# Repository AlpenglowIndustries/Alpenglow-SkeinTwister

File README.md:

# Alpenglow-SkeinTwister
The main open-source hardware repo for the Alpenglow Yarn SkeinTwister.  Start here, repo for the SkeinTwister software is [here](https://github.com/AlpenglowIndustries/SkeinTwisterCode).

Hello my friends.  As one of the final acts of Alpenglow Industries, we are open-sourcing the SkeinTwister design under a permissive CERN open hardware v2 license.  The text of the license is included in this repo, what it practically means is that as long as you attribute our original work, you can reproduce anything in this repo and even sell it.  

The [Alpenglow YouTube channel](https://www.youtube.com/watch?v=4FvFv4GcJJE&list=PLGswnsgctcE1kCAfXg5c3xEA6l_XDLfXw&pp=sAgC) has videos on assembly/disassembly and repair.

Note that we were purchasing parts and materials in large batches, so our sources that are listed in the SkeinTwister BOM spreadsheet may or may not be relevant for you. Use it as a starting point. The ReadMe docs in each folder will have more info about the parts that folder describes.

If you would like to reproduce this design and need help, Carrie Sundra is available to hire for consulting and for manufacturing the custom circuit boards.  You can reach out to her via [Discord](https://discord.com/users/461976578734161920) or [this email](mailto:info@alpenglowyarn.com) for now.  She is willing to do one free 30 minute video chat with anyone who is interested in reproducing the design, after that she may have time available at her hourly consulting rate.

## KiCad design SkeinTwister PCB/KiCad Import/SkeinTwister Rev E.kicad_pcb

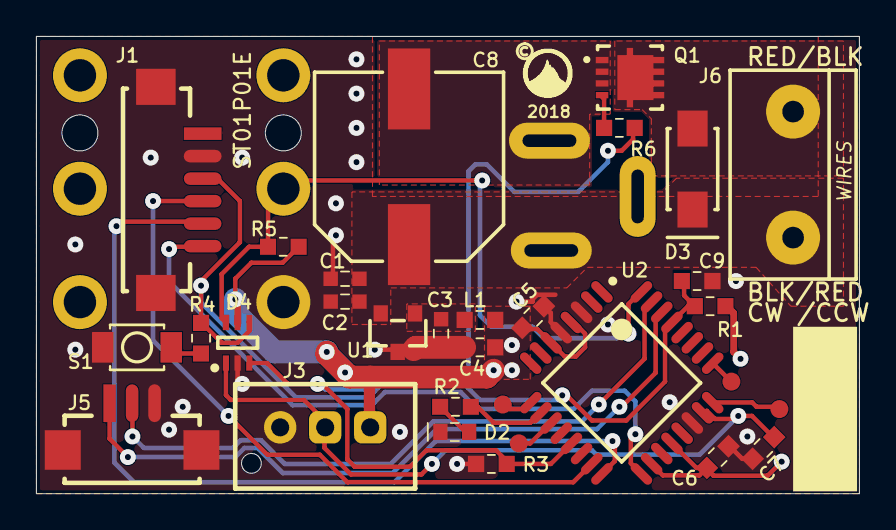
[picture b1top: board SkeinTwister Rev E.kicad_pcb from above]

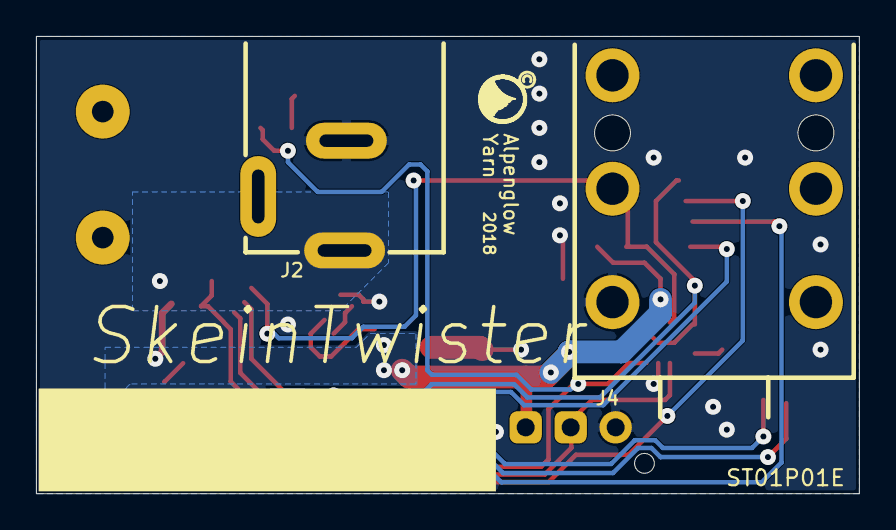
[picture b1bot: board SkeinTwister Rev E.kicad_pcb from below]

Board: 2 copper layers, 45.7 x 25.4 mm, 33 parts (2 on the bottom side), 22 nets.

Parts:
C1: 1.0; 0603
C2, C3, C5, C6, C7, C9: 0.1; 0603
C4: 10; 0603
C8: 820; CAP-10MM
D2: LED; 0603+
D3: DIODE, SM SIG; SMA
D4: TVS; SOT-363
J1: ISP Program; DF13C-6P-1.25V
J2: POWER; CONN-JACK-2MM - slots - M3
J3: KNOB; JST-XH-3
J4: FOOT PEDAL; AUDIO-6.35MM-RTA
J5: SERIAL; DF13C-3P-1.25V
J6: ?; OSTTE021104
L1: FERRITE, 0603; 0603
Q1: N; DFN8_3X3MM
R1, R3, R5: 10.0k; 0603
R2: 1.00k; 0603
R4: DNP (100); 0603
R6: 100; 0603
S1: DNP; PB-3.0X2.5-SMT
TP1, TP2, TP3, TP4: TESTPOINT; TP-1.0MM
U1: TLV76050; SOT-23
U2: ATMEGA328P_v2; TQFP-32

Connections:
5V: C4.1, C5.1, C6.1, D4.5, J3.3, L1.2, R1.2, R5.2, U2.4, U2.6, U2.18, U2.20
5V_UF: C3.1, L1.1, U1.1
12V: C1.1, C2.1, C8.1, D3.K, J2.1, J6.1, U1.2
FOOTPEDAL: D4.6, J4.4, R5.1, U2.32
GND: C1.2, C2.2, C3.2, C4.2, C5.2, C6.2, C7.2, C8.2, C9.2, D2.2, D4.2, J1.2, J1.7, J1.8, J2.2, J3.1, J4.6, J5.3, J5.4, J5.5, Q1.S, R3.1, S1.1, U1.3, U2.3, U2.5, U2.22
KNOB: C7.1, D4.1, J3.2, U2.23
LED: R2.2, U2.10
MISO: J1.5, U2.16
MOSI: J1.4, U2.15
NetD2_1: D2.1, R2.1
NetD3_A: D3.A, J6.2, Q1.D
NetQ1_G: Q1.G, R6.1
NetR4_2: R4.2, S1.2
NetTP1_1: TP1.1, U2.25
NetTP2_1: TP2.1, U2.24
NetTP3_1: TP3.1, U2.9
NetTP4_1: TP4.1, U2.11
ON/OFF: D4.3, R3.2, R6.2, U2.13
RESET: C9.1, D4.4, J1.3, R1.1, R4.1, U2.29
RXD: J5.1, U2.30
SCK: J1.6, U2.17
TXD: J5.2, U2.31

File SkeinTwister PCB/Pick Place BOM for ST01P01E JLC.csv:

Designator,Comment,Layer,Footprint,Mid X,Mid Y,Rotation
C1,1,Top,0603,17.145,11.938,180
C2,0.1,Top,0603,17.145,10.668,180
C3,0.1,Top,0603,22.479,8.89,270
C4,10,Top,0603,24.6379,8.1279,180
C5,0.1,Top,0603,27.593,9.813,45
C6,0.1,Top,0603,37.846,2.0322,45
C7,0.1,Top,0603,40.386,2.5399,225
C8,820,Top,CAP-10MM,20.701,18.161,90
C9,0.1,Top,0603,36.7031,11.8111,360
D2,LED,Top,0603+,23.241,3.429,180
D3,"DIODE, SM SIG",Top,SMA,36.449,18.034,90
D4,TVS,Top,SOT-363,11.176,8.382,90
J1,ISP Program,Top,DF13C-6P-1.25V,7.934,16.875,270
J2,POWER,Bottom,CONN-JACK-2MM_-_slots_-_M3,30.951,16.56,180
J3,KNOB,Top,JST-XH-3,15.242,2.683,180
J4,FOOT PEDAL,Bottom,AUDIO-6.35MM-RTA,8.066,16.941,180
J5,SERIAL,Top,DF13C-3P-1.25V,5.314,3.726,360
J6,?,Top,OSTTE021104,42.037,17.724,90
L1,"FERRITE, 0603",Top,0603,24.6381,9.6521,360
Q1,N,Top,DFN8_3X3MM,32.974,23.114,360
R1,10.0k,Top,0603,37.426,10.414,360
R2,1.00k,Top,0603,23.28,4.826,0
R3,10.0k,Top,0603,25.2731,1.6511,0
R4,DNP (100),Top,0603,9.1441,8.6359,270
R5,10.0k,Top,0603,13.7161,13.7161,360
R6,100,Top,0603,32.3851,20.3201,360
S1,DNP,Top,PB-3.0X2.5-SMT,5.5881,8.1281,360
TP1,TESTPOINT,Top,TP-1.0MM,38.608,6.223,90
TP2,TESTPOINT,Top,TP-1.0MM,41.275,4.699,90
TP3,TESTPOINT,Top,TP-1.0MM,25.908,4.953,90
TP4,TESTPOINT,Top,TP-1.0MM,26.797,2.794,90
U1,TLV76050,Top,SOT-23,20.0787,8.944,180
U2,ATMEGA328P_v2,Top,TQFP-32,32.5129,6.1528,315
